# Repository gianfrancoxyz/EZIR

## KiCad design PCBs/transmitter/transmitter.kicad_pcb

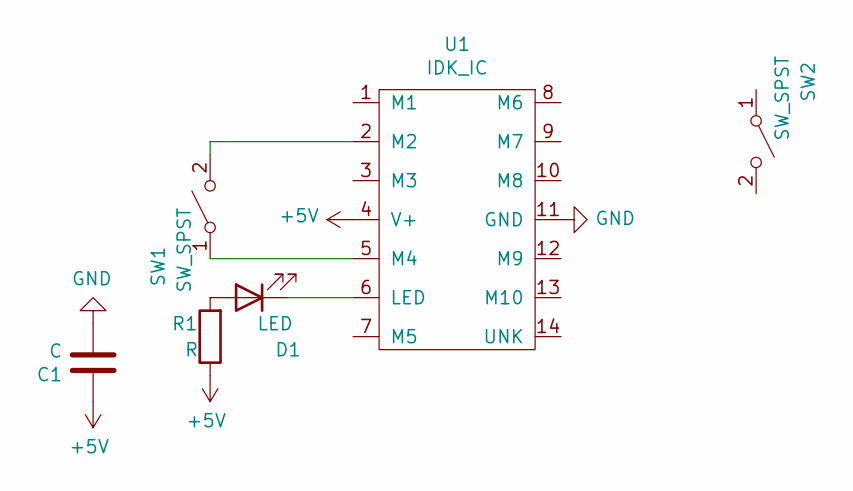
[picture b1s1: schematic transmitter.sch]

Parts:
C1: C; R_0805_2012Metric_Pad1.20x1.40mm_HandSolder
D1: LED; LED_D1.8mm_W3.3mm_H2.4mm
R1: R; R_0805_2012Metric_Pad1.20x1.40mm_HandSolder
SW1, SW2: SW_SPST; SW_Cherry_MX_1.00u_PCB
U1: IDK_IC; SO-14_3.9x8.65mm_P1.27mm

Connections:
+5V: C1.2, R1.1, U1.4 (V+)
GND: C1.1, U1.11 (GND)
unnamed: D1.1 (K), U1.6 (LED)
unnamed: D1.2 (A), R1.2
unnamed: SW1.1 (A), U1.5 (M4)
unnamed: SW1.2 (B), U1.2 (M2)

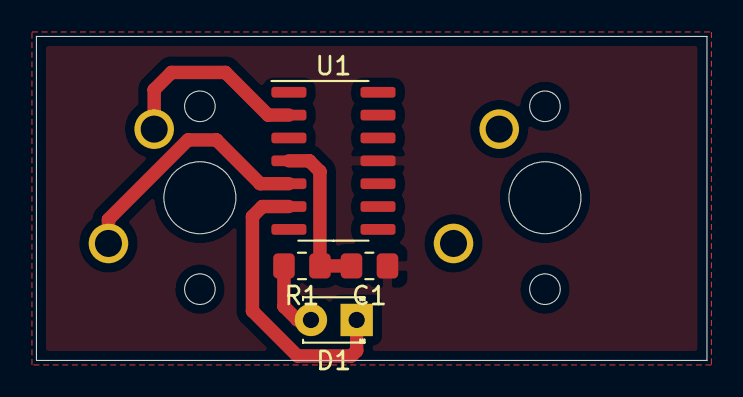
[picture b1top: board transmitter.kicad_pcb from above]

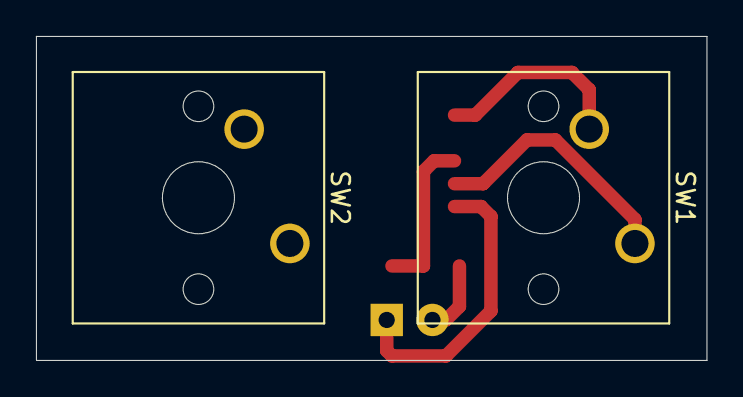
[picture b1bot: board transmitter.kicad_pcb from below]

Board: 2 copper layers, 37.2 x 18.0 mm, 6 parts (2 on the bottom side), 6 nets.

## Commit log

2021-02-16 Added receiver PCB minus pwr src
